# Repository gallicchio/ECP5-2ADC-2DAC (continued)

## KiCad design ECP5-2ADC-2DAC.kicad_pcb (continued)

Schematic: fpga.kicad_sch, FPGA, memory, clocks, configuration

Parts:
C5401, C5411, C5422, C5424, C5431, C5502, C5503, C5504, C5505, C5701, C5711: 100nF; C_0402_1005Metric; LCSC C1525
C5421: 10nF; C_0402_1005Metric; LCSC C15195
C5501, C5802, C5803, C5804, C5811, C5821, C5822, C5823, C5824, C5825, C5826, C5827: 10uF; C_0603_1608Metric; LCSC C96446
C5801: 22uF; C_0805_2012Metric; LCSC C45783
C5805, C5806, C5807, C5808, C5809, C5810, C5812, C5813, C5831, C5832, C5833, C5834, C5835, C5836, C5837, C5838, C5839, C5840, C5841, C5842, C5843: 100nF; C_0402_1005Metric_BGA; LCSC C1525
C5851, C5852, C5853, C5854, C5855, C5856, C5857: 22nF; C_0402_1005Metric_BGA; LCSC C1532
D301, D302, D303, D304, D305, D306, D307, D308: white; LED_0603_1608Metric; LCSC C2290
D309: XL-1615RGBC-RF; LED-ARRAY-SMD_4P-L1.6-W1.5-BR_XL-1615RGBC-RF; LCSC C965840
FB5811: 600R@100MHz; L_0603_1608Metric; LCSC C85833
J301, J302: SMA; SMA_BAT_Wireless_BWSMA-KWE-Z001; LCSC C496551
J303: PMOD A; PinSocket_2x06_P2.54mm_Horizontal; LCSC C22373932
J304: PMOD B; PinSocket_2x06_P2.54mm_Horizontal; LCSC C22373932
J305: JTAG; PinHeader_1x06_P2.54mm_Vertical; LCSC C2337
JP3001: TERM; PinHeader_1x02_P2.54mm_Vertical; LCSC C2337
R5401, R5411, R5412, R5413, R5423, R5601, R5602, R5603, R5604, R5605, R5606, R5607, R5608, R5611, R5612, R5613, R5614, R5615, R5616, R5617, R5618: 33R; R_0603_1608Metric; LCSC C23140
R5416, R5417, R5711, R5712, R5713, R5721, R5722, R5723, R5724: 4.7k; R_0603_1608Metric; LCSC C23162
R5421, R5431: 49.9R; R_0603_1608Metric; LCSC C23185
R5424, R5425, R5426, R5451, R5452, R5701, R5702, R5703: 10k; R_0603_1608Metric; LCSC C25804
R5427, R5441, R5442, R5443, R5444, R5445, R5446, R5447, R5448: 1k; R_0603_1608Metric; LCSC C21190
R5461, R5462, R5463: 330R; R_0603_1608Metric; LCSC C23138
SW301, SW302, SW303: SW_Push; SW-SMD_L3.9-W3.0-P4.45; LCSC C720477
U1: LFE5U-25F-6BG256C; BGA-256_14.0x14.0mm_Layout16x16_P0.8mm_Ball0.45mm_Pad0.32mm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; LCSC C1521614
U301: Si5351A-B-GTR; MSOP-10_3x3mm_P0.5mm; LCSC C504891
U302: TLV3501AIDBVR; SOT-23-6; LCSC C193413
U304: SN74LVC1G17DBVR; SOT-23-5; LCSC C7836
U305: W9825G6KH-6; TSOP-II-54_22.2x10.16mm_P0.8mm; LCSC C62246
U306: W25Q128JVSIQ; SOIC-8_5.3x5.3mm_P1.27mm; LCSC C97521
X301: FT5HNBPK25.0-T1; Oscillator_SMD_Fox_FT5H_5.0x3.2mm; LCSC C5742665
Y301: 25MHz; Crystal_SMD_3225-4Pin_3.2x2.5mm; LCSC C362338

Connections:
+1V1: C5801.1, C5802.1, C5803.1, C5804.1, C5805.1, C5806.1, C5807.1, C5808.1, C5809.1, C5810.1, U1.G6 (VCC), U1.G7 (VCC), U1.G9 (VCC), U1.L8 (VCC), U1.L9 (VCC), U1.L10 (VCC); also elsewhere on the board
+2V5: FB5811.1; also elsewhere on the board
+2V5_AUX: C5811.1, C5812.1, C5813.1, FB5811.2, U1.G11 (VCCAUX), U1.L7 (VCCAUX)
+3V3: C5401.1, C5411.1, C5431.1, C5501.1, C5502.1, C5503.1, C5504.1, C5505.1, C5701.1, C5821.1, C5822.1, C5823.1, C5824.1, C5825.1, C5826.1, C5827.1, C5831.1, C5832.1, C5833.1, C5834.1, C5835.1, C5836.1, C5837.1, C5838.1, C5839.1, C5840.1, C5841.1, C5842.1, C5843.1, C5851.1, C5852.1, C5853.1, C5854.1, C5855.1, C5856.1, C5857.1, D309.2 (A), J303.11, J303.12, J304.11, J304.12, J305.1, R5416.2, R5417.2, R5451.1, R5452.1, R5701.1, R5702.1, R5703.1, R5711.1, R5712.1, R5713.1, R5721.2, R5722.2, R5723.2, U1.F6 (VCCIO0), U1.F7 (VCCIO0), U1.F10 (VCCIO1), U1.F11 (VCCIO1), U1.H6 (VCCIO7), U1.H7 (VCCIO7), U1.H11 (VCCIO2), U1.J6 (VCCIO6), U1.J7 (VCCIO6), U1.J11 (VCCIO2), U1.K11 (VCCIO3), U1.L6 (VCCIO8), U1.L11 (VCCIO3), U1.P10 (P10_CFG1), U301.1 (VDD), U301.7 (VDDO), U304.5 (VCC), U305.1 (VDD), U305.3 (VDDQ), U305.9 (VDDQ), U305.14 (VDD), U305.27 (VDD), U305.43 (VDDQ), U305.49 (VDDQ), U306.8 (VCC), X301.4 (VCC); also elsewhere on the board
+3V3_ADC: C5422.1, R5424.1, U302.4 (V+); also elsewhere on the board
/ADC/ADC_A_CLK: U1.E4; also elsewhere on the board
/ADC/ADC_A_D0: U1.D1; also elsewhere on the board
/ADC/ADC_A_D1: U1.C1; also elsewhere on the board
/ADC/ADC_A_D2: U1.C2; also elsewhere on the board
/ADC/ADC_A_D3: U1.B1; also elsewhere on the board
/ADC/ADC_A_D4: U1.B2; also elsewhere on the board
/ADC/ADC_A_D5: U1.C3; also elsewhere on the board
/ADC/ADC_A_D6: U1.D3; also elsewhere on the board
/ADC/ADC_A_D7: U1.E3; also elsewhere on the board
/ADC/ADC_A_D8: U1.F3; also elsewhere on the board
/ADC/ADC_A_D9: U1.G3; also elsewhere on the board
/ADC/ADC_A_D10: U1.H3; also elsewhere on the board
/ADC/ADC_A_D11: U1.J5; also elsewhere on the board
/ADC/ADC_A_OTR: U1.J3 (J3_PCLK); also elsewhere on the board
/ADC/ADC_B_CLK: U1.R2; also elsewhere on the board
/ADC/ADC_B_D0: U1.G5; also elsewhere on the board
/ADC/ADC_B_D1: U1.F4; also elsewhere on the board
/ADC/ADC_B_D2: U1.G4; also elsewhere on the board
/ADC/ADC_B_D3: U1.H4; also elsewhere on the board
/ADC/ADC_B_D4: U1.J4; also elsewhere on the board
/ADC/ADC_B_D5: U1.K3; also elsewhere on the board
/ADC/ADC_B_D6: U1.H2; also elsewhere on the board
/ADC/ADC_B_D7: U1.G1 (G1_PCLK); also elsewhere on the board
/ADC/ADC_B_D8: U1.G2; also elsewhere on the board
/ADC/ADC_B_D9: U1.F1; also elsewhere on the board
/ADC/ADC_B_D10: U1.F2; also elsewhere on the board
/ADC/ADC_B_D11: U1.E1; also elsewhere on the board
/ADC/ADC_B_OTR: U1.E2; also elsewhere on the board
/ADC/ADC_DCS: U1.T6; also elsewhere on the board
/ADC/ADC_DFS: U1.R6; also elsewhere on the board
/ADC/ADC_PDWN_A: U1.R7; also elsewhere on the board
/ADC/ADC_PDWN_B: U1.T4; also elsewhere on the board
/DAC/DAC_CLK1: U1.N6; also elsewhere on the board
/DAC/DAC_CLK2: U1.M9; also elsewhere on the board
/DAC/DAC_MODE: U1.R8; also elsewhere on the board
/DAC/DAC_P1_D0: U1.L5; also elsewhere on the board
/DAC/DAC_P1_D1: U1.K5; also elsewhere on the board
/DAC/DAC_P1_D2: U1.N4; also elsewhere on the board
/DAC/DAC_P1_D3: U1.M4; also elsewhere on the board
/DAC/DAC_P1_D4: U1.L4 (L4_PCLK); also elsewhere on the board
/DAC/DAC_P1_D5: U1.K4 (K4_PCLK); also elsewhere on the board
/DAC/DAC_P1_D6: U1.P7; also elsewhere on the board
/DAC/DAC_P1_D7: U1.P6; also elsewhere on the board
/DAC/DAC_P1_D8: U1.P5; also elsewhere on the board
/DAC/DAC_P1_D9: U1.P4; also elsewhere on the board
/DAC/DAC_P1_D10: U1.P3; also elsewhere on the board
/DAC/DAC_P1_D11: U1.N3; also elsewhere on the board
/DAC/DAC_P1_D12: U1.M3; also elsewhere on the board
/DAC/DAC_P1_D13: U1.L3; also elsewhere on the board
/DAC/DAC_P2_D0: U1.L1 (L1_PCLK); also elsewhere on the board
/DAC/DAC_P2_D1: U1.L2 (L2_PCLK); also elsewhere on the board
/DAC/DAC_P2_D2: U1.M1 (M1_PCLK); also elsewhere on the board
/DAC/DAC_P2_D3: U1.M2 (M2_PCLK); also elsewhere on the board
/DAC/DAC_P2_D4: U1.N1; also elsewhere on the board
/DAC/DAC_P2_D5: U1.P1; also elsewhere on the board
/DAC/DAC_P2_D6: U1.P2; also elsewhere on the board
/DAC/DAC_P2_D7: U1.R1; also elsewhere on the board
/DAC/DAC_P2_D8: U1.T2; also elsewhere on the board
/DAC/DAC_P2_D9: U1.R3; also elsewhere on the board
/DAC/DAC_P2_D10: U1.T3; also elsewhere on the board
/DAC/DAC_P2_D11: U1.R4; also elsewhere on the board
/DAC/DAC_P2_D12: U1.M6; also elsewhere on the board
/DAC/DAC_P2_D13: U1.M5; also elsewhere on the board
/DAC/DAC_SLEEP: U1.R5; also elsewhere on the board
/DAC/DAC_WRT1: U1.N5; also elsewhere on the board
/DAC/DAC_WRT2: U1.P8; also elsewhere on the board
/FPGA, memory, clocks, configuration/CLK_EXT: R5423.2, U1.K2 (K2_PCLK)
/FPGA, memory, clocks, configuration/CLK_SI2: R5413.2, U1.K1 (K1_PCLK)
/FPGA, memory, clocks, configuration/ETH_INT_N: U1.F12; also elsewhere on the board
/FPGA, memory, clocks, configuration/ETH_MDC: U1.F15; also elsewhere on the board
/FPGA, memory, clocks, configuration/ETH_MDIO: U1.F16; also elsewhere on the board
/FPGA, memory, clocks, configuration/ETH_RST_N: U1.E16; also elsewhere on the board
/FPGA, memory, clocks, configuration/ETH_RXC: U1.E8 (E8_PCLK); also elsewhere on the board
/FPGA, memory, clocks, configuration/ETH_RXD0: U1.F14; also elsewhere on the board
/FPGA, memory, clocks, configuration/ETH_RXD1: U1.E14; also elsewhere on the board
/FPGA, memory, clocks, configuration/ETH_RXD2: U1.D14; also elsewhere on the board
/FPGA, memory, clocks, configuration/ETH_RXD3: U1.C14; also elsewhere on the board
/FPGA, memory, clocks, configuration/ETH_RX_CTL: U1.F13; also elsewhere on the board
/FPGA, memory, clocks, configuration/ETH_TXC: U1.E15; also elsewhere on the board
/FPGA, memory, clocks, configuration/ETH_TXD0: U1.C16; also elsewhere on the board
/FPGA, memory, clocks, configuration/ETH_TXD1: U1.C15; also elsewhere on the board
/FPGA, memory, clocks, configuration/ETH_TXD2: U1.B16; also elsewhere on the board
/FPGA, memory, clocks, configuration/ETH_TXD3: U1.B15; also elsewhere on the board
/FPGA, memory, clocks, configuration/ETH_TX_CTL: U1.D16; also elsewhere on the board
/FPGA, memory, clocks, configuration/FTDI_DTR: U1.G15; also elsewhere on the board
/FPGA, memory, clocks, configuration/FTDI_RTS: U1.G16 (G16_PCLK); also elsewhere on the board
/FPGA, memory, clocks, configuration/GPDI_CEC: U1.K12; also elsewhere on the board
/FPGA, memory, clocks, configuration/GPDI_CK_N: U1.K15 (K15_PCLK); also elsewhere on the board
/FPGA, memory, clocks, configuration/GPDI_CK_P: U1.K16 (K16_PCLK); also elsewhere on the board
/FPGA, memory, clocks, configuration/GPDI_D0_N: U1.J15 (J15_PCLK); also elsewhere on the board
/FPGA, memory, clocks, configuration/GPDI_D0_P: U1.J16 (J16_PCLK); also elsewhere on the board
/FPGA, memory, clocks, configuration/GPDI_D1_N: U1.K14; also elsewhere on the board
/FPGA, memory, clocks, configuration/GPDI_D1_P: U1.J14 (J14_PCLK); also elsewhere on the board
/FPGA, memory, clocks, configuration/GPDI_D2_N: U1.J12; also elsewhere on the board
/FPGA, memory, clocks, configuration/GPDI_D2_P: U1.J13; also elsewhere on the board
/FPGA, memory, clocks, configuration/GPDI_HPD: U1.K13 (K13_PCLK); also elsewhere on the board
/FPGA, memory, clocks, configuration/GPDI_SCL: U1.M12; also elsewhere on the board
/FPGA, memory, clocks, configuration/GPDI_SDA: U1.N13; also elsewhere on the board
/FPGA, memory, clocks, configuration/I2C_SCL: R5417.1, U1.A15, U301.4 (SCL)
/FPGA, memory, clocks, configuration/I2C_SDA: R5416.1, U1.E13, U301.5 (SDA)
/FPGA, memory, clocks, configuration/JTAG_TCK: J305.2, R5724.1, U1.T10 (T10_TCK); also elsewhere on the board
/FPGA, memory, clocks, configuration/JTAG_TDI: J305.4, R5722.1, U1.R11 (R11_TDI); also elsewhere on the board
/FPGA, memory, clocks, configuration/JTAG_TDO: J305.5, R5723.1, U1.M10 (M10_TDO); also elsewhere on the board
/FPGA, memory, clocks, configuration/JTAG_TMS: J305.3, R5721.1, U1.T11 (T11_TMS); also elsewhere on the board
/FPGA, memory, clocks, configuration/LED2: R5443.1, U1.E10
/FPGA, memory, clocks, configuration/LED3: R5444.1, U1.E11
/FPGA, memory, clocks, configuration/LED4: R5445.1, U1.G12
/FPGA, memory, clocks, configuration/LED5: R5446.1, U1.E12
/FPGA, memory, clocks, configuration/LED6: R5447.1, U1.A14
/FPGA, memory, clocks, configuration/LED7: R5448.1, U1.B14
/FPGA, memory, clocks, configuration/LED_B: R5463.1, U1.R12
/FPGA, memory, clocks, configuration/LED_G: R5462.1, U1.R13
/FPGA, memory, clocks, configuration/LED_R: R5461.1, U1.R14
/FPGA, memory, clocks, configuration/PMODA_0: R5601.1, U1.R15
/FPGA, memory, clocks, configuration/PMODA_1: R5602.1, U1.P15
/FPGA, memory, clocks, configuration/PMODA_2: R5603.1, U1.N16
/FPGA, memory, clocks, configuration/PMODA_3: R5604.1, U1.M16 (M16_PCLK)
/FPGA, memory, clocks, configuration/PMODA_4: R5605.2, U1.R16
/FPGA, memory, clocks, configuration/PMODA_5: R5606.2, U1.P16
/FPGA, memory, clocks, configuration/PMODA_6: R5607.2, U1.M15 (M15_PCLK)
/FPGA, memory, clocks, configuration/PMODA_7: R5608.2, U1.L15 (L15_PCLK)
/FPGA, memory, clocks, configuration/PMODB_0: R5611.1, U1.L16 (L16_PCLK)
/FPGA, memory, clocks, configuration/PMODB_1: R5612.1, U1.N14
/FPGA, memory, clocks, configuration/PMODB_2: R5613.1, U1.M14
/FPGA, memory, clocks, configuration/PMODB_3: R5614.1, U1.L14
/FPGA, memory, clocks, configuration/PMODB_4: R5615.2, U1.P14
/FPGA, memory, clocks, configuration/PMODB_5: R5616.2, U1.M13
/FPGA, memory, clocks, configuration/PMODB_6: R5617.2, U1.L13 (L13_PCLK)
/FPGA, memory, clocks, configuration/PMODB_7: R5618.2, U1.L12
/FPGA, memory, clocks, configuration/SDRAM_A0: U1.A5, U305.23 (A0)
/FPGA, memory, clocks, configuration/SDRAM_A1: U1.B5, U305.24 (A1)
/FPGA, memory, clocks, configuration/SDRAM_A2: U1.A4, U305.25 (A2)
/FPGA, memory, clocks, configuration/SDRAM_A3: U1.B4, U305.26 (A3)
/FPGA, memory, clocks, configuration/SDRAM_A4: U1.B13, U305.29 (A4)
/FPGA, memory, clocks, configuration/SDRAM_A5: U1.A13, U305.30 (A5)
/FPGA, memory, clocks, configuration/SDRAM_A6: U1.B12, U305.31 (A6)
/FPGA, memory, clocks, configuration/SDRAM_A7: U1.A12, U305.32 (A7)
/FPGA, memory, clocks, configuration/SDRAM_A8: U1.B11, U305.33 (A8)
/FPGA, memory, clocks, configuration/SDRAM_A9: U1.A11, U305.34 (A9)
/FPGA, memory, clocks, configuration/SDRAM_A10: U1.B6, U305.22 (A10)
/FPGA, memory, clocks, configuration/SDRAM_A11: U1.B10, U305.35 (A11)
/FPGA, memory, clocks, configuration/SDRAM_A12: U1.C13, U305.36 (A12)
/FPGA, memory, clocks, configuration/SDRAM_BA0: U1.B7 (B7_PCLK), U305.20 (BA0)
/FPGA, memory, clocks, configuration/SDRAM_BA1: U1.A6, U305.21 (BA1)
/FPGA, memory, clocks, configuration/SDRAM_CAS_N: U1.A8 (A8_PCLK), U305.17 (~CAS)
/FPGA, memory, clocks, configuration/SDRAM_CKE: U1.C12, U305.37 (CKE)
/FPGA, memory, clocks, configuration/SDRAM_CLK: U1.C11, U305.38 (CLK)
/FPGA, memory, clocks, configuration/SDRAM_CS_N: U1.A7 (A7_PCLK), U305.19 (~CS)
/FPGA, memory, clocks, configuration/SDRAM_DQ0: U1.D6, U305.2 (DQ0)
/FPGA, memory, clocks, configuration/SDRAM_DQ1: U1.D5, U305.4 (DQ1)
/FPGA, memory, clocks, configuration/SDRAM_DQ2: U1.D4, U305.5 (DQ2)
/FPGA, memory, clocks, configuration/SDRAM_DQ3: U1.C6, U305.7 (DQ3)
/FPGA, memory, clocks, configuration/SDRAM_DQ4: U1.C5, U305.8 (DQ4)
/FPGA, memory, clocks, configuration/SDRAM_DQ5: U1.C4, U305.10 (DQ5)
/FPGA, memory, clocks, configuration/SDRAM_DQ6: U1.A10, U305.11 (DQ6)
/FPGA, memory, clocks, configuration/SDRAM_DQ7: U1.B9 (B9_PCLK), U305.13 (DQ7)
/FPGA, memory, clocks, configuration/SDRAM_DQ8: U1.C9 (C9_PCLK), U305.42 (DQ8)
/FPGA, memory, clocks, configuration/SDRAM_DQ9: U1.C8 (C8_PCLK), U305.44 (DQ9)
/FPGA, memory, clocks, configuration/SDRAM_DQ10: U1.D13, U305.45 (DQ10)
/FPGA, memory, clocks, configuration/SDRAM_DQ11: U1.D12, U305.47 (DQ11)
/FPGA, memory, clocks, configuration/SDRAM_DQ12: U1.D11, U305.48 (DQ12)
/FPGA, memory, clocks, configuration/SDRAM_DQ13: U1.D10, U305.50 (DQ13)
/FPGA, memory, clocks, configuration/SDRAM_DQ14: U1.D9, U305.51 (DQ14)
/FPGA, memory, clocks, configuration/SDRAM_DQ15: U1.D8 (D8_PCLK), U305.53 (DQ15)
/FPGA, memory, clocks, configuration/SDRAM_DQMH: U1.C10, U305.39 (DQMH)
/FPGA, memory, clocks, configuration/SDRAM_DQML: U1.A9, U305.15 (DQML)
/FPGA, memory, clocks, configuration/SDRAM_RAS_N: U1.B8 (B8_PCLK), U305.18 (~RAS)
/FPGA, memory, clocks, configuration/SDRAM_WE_N: U1.E9, U305.16 (~WE)
/FPGA, memory, clocks, configuration/SD_CLK: U1.T15; also elsewhere on the board
/FPGA, memory, clocks, configuration/SD_CMD: U1.P12; also elsewhere on the board
/FPGA, memory, clocks, configuration/SD_D0: U1.T14; also elsewhere on the board
/FPGA, memory, clocks, configuration/SD_D1: U1.T13; also elsewhere on the board
/FPGA, memory, clocks, configuration/SD_D2: U1.P13; also elsewhere on the board
/FPGA, memory, clocks, configuration/SD_D3: U1.N12; also elsewhere on the board
/FPGA, memory, clocks, configuration/UART_RX: U1.H15; also elsewhere on the board
/FPGA, memory, clocks, configuration/UART_TX: U1.H14; also elsewhere on the board
/FPGA, memory, clocks, configuration/USB_DN: U1.G13; also elsewhere on the board
/FPGA, memory, clocks, configuration/USB_DP: U1.G14; also elsewhere on the board
/FPGA, memory, clocks, configuration/USB_PULLUP: U1.H13; also elsewhere on the board
GND: C5401.2, C5411.2, C5422.2, C5424.2, C5431.2, C5501.2, C5502.2, C5503.2, C5504.2, C5505.2, C5701.2, C5711.2, C5801.2, C5802.2, C5803.2, C5804.2, C5805.2, C5806.2, C5807.2, C5808.2, C5809.2, C5810.2, C5811.2, C5812.2, C5813.2, C5821.2, C5822.2, C5823.2, C5824.2, C5825.2, C5826.2, C5827.2, C5831.2, C5832.2, C5833.2, C5834.2, C5835.2, C5836.2, C5837.2, C5838.2, C5839.2, C5840.2, C5841.2, C5842.2, C5843.2, C5851.2, C5852.2, C5853.2, C5854.2, C5855.2, C5856.2, C5857.2, D301.1 (K), D302.1 (K), D303.1 (K), D304.1 (K), D305.1 (K), D306.1 (K), D307.1 (K), D308.1 (K), J301.2, J302.2, J303.9, J303.10, J304.9, J304.10, J305.6, JP3001.1 (A), R5425.2, R5724.2, SW301.1, SW302.1, SW303.2, U1.A1 (GND), U1.A16 (GND), U1.D2 (GND), U1.D15 (GND), U1.F8 (GND), U1.F9 (GND), U1.G8 (GND), U1.G10 (GND), U1.H1 (GND), U1.H8 (GND), U1.H9 (GND), U1.H10 (GND), U1.H16 (GND), U1.J8 (GND), U1.J9 (GND), U1.J10 (GND), U1.K6 (GND), U1.K7 (GND), U1.K8 (GND), U1.K9 (GND), U1.K10 (GND), U1.N2 (GND), U1.N10 (N10_CFG0), U1.N15 (GND), U1.R10 (R10_CFG2), U1.T1 (GND), U1.T5 (GND), U1.T12 (GND), U1.T16 (GND), U301.8 (GND), U302.2 (V-), U302.6 (SHDN), U304.3 (GND), U305.6 (VSSQ), U305.12 (VSSQ), U305.28 (VSS), U305.41 (VSS), U305.46 (VSSQ), U305.52 (VSSQ), U305.54 (VSS), U306.4 (GND), X301.1 (GND), X301.2 (GND), Y301.2 (G), Y301.4 (G); also elsewhere on the board
unnamed: C5421.1, J301.1, R5421.1
unnamed: C5421.2, R5427.1
unnamed: D301.2 (A), R5441.2
unnamed: D302.2 (A), R5442.2
unnamed: D303.2 (A), R5443.2
unnamed: D304.2 (A), R5444.2
unnamed: D305.2 (A), R5445.2
unnamed: D306.2 (A), R5446.2
unnamed: D307.2 (A), R5447.2
unnamed: D308.2 (A), R5448.2
unnamed: D309.3 (B), R5463.2
unnamed: D309.4 (G), R5462.2
unnamed: D309.1 (R), R5461.2
unnamed: J302.1, R5431.2
unnamed: J303.1, R5601.2
unnamed: J303.2, R5605.1
unnamed: J303.3, R5602.2
unnamed: J303.4, R5606.1
unnamed: J303.5, R5603.2
unnamed: J303.6, R5607.1
unnamed: J303.7, R5604.2
unnamed: J303.8, R5608.1
unnamed: J304.1, R5611.2
unnamed: J304.2, R5615.1
unnamed: J304.3, R5612.2
unnamed: J304.4, R5616.1
unnamed: J304.5, R5613.2
unnamed: J304.6, R5617.1
unnamed: J304.7, R5614.2
unnamed: J304.8, R5618.1
unnamed: JP3001.2 (B), R5421.2
unnamed: R5423.1, U302.5
unnamed: R5431.1, U304.4
unnamed: R5441.1, U1.E6
unnamed: R5442.1, U1.E5
unnamed: R5451.2, SW301.2, U1.A3
unnamed: R5452.2, SW302.2, U1.B3
unnamed: U1.A2, U304.2
unnamed: R5401.2, U1.C7 (C7_PCLK)
unnamed: R5411.2, U1.D7 (D7_PCLK)
unnamed: R5412.2, U1.E7 (E7_PCLK)
unnamed: U1.N9 (N9_CCLK/MCLK), U306.6 (CLK)
unnamed: R5713.2, U1.P9 (P9_DONE)
unnamed: C5711.1, R5711.2, SW303.1, U1.R9 (R9_PROGRAMN)
unnamed: R5712.2, U1.T9 (T9_INITN)
unnamed: R5411.1, U301.10 (CLK0)
unnamed: R5412.1, U301.9 (CLK1)
unnamed: R5413.1, U301.6 (CLK2)
unnamed: U301.2 (XA), Y301.1
unnamed: U301.3 (XB), Y301.3
unnamed: R5426.1, R5427.2, U302.3 (+)
unnamed: C5424.1, R5424.2, R5425.1, R5426.2, U302.1 (-)
unnamed: U1.T8, U306.5 (DI/IO0)
unnamed: U1.T7, U306.2 (DO/IO1)
unnamed: R5703.2, U1.N8, U306.1 (~CS)
unnamed: R5702.2, U1.N7, U306.7 (~HOLD/IO3)
unnamed: R5701.2, U1.M7, U306.3 (~WP/IO2)
unnamed: R5401.1, X301.3 (OUT)

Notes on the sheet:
PROGRAMN, INITN, DONE: 4.7 k to VCCIO8
press: reload from the flash
VCCIO: 100 nF per pin
Si5351A: three programmable clocks, 2.5 kHz to 200 MHz
FPGA: Lattice ECP5 LFE5U-25F-6BG256C, 32 MB SDRAM, 16 MB flash, clocks, configuration
10 pF crystal, load capacitors inside; this I2C bus is the Si5351's alone (the HDMI DDC is a second bus)
bank 3: SD card, USB, serial, Pmods
CLK IN: an external reference or sample clock
quad SPI flash on the sysCONFIG pins: boots the FPGA and holds the bitstream
100 nF: configuration starts 0.5 ms after VCCIO8
I2C pull-ups
bank 8: sysCONFIG, flash, JTAG, slow controls
4.7 k: TMS, TDI, TDO up; TCK down
VCCIO: 10 µF per bank
bank 7: ADC
15 of the 39 SDRAM lines live on bank 0
shunt in = 50 Ω
VCCAUX: ferrite + 10 µF + 100 nF per pin
user LEDs 0-7, white, active high, ~1 mA
RGB LED (common anode): drive a cathode low to light it, ~2 mA
SDRAM: 100 nF per VDD/VDDQ pair
FPGA power: 6 x VCC (1.1 V core), 2 x VCCAUX (2.5 V through a ferrite), 13 x VCCIO (3.3 V, all banks), 27 x GND
VCCIO: 22 nF per bank (as the Icepi Zero)
CFG[2:0] = 010: master SPI boot from the flash (as the Icepi Zero)
mid-rail 1.65 V: -IN directly, +IN through 10 k
CLK OUT: sync a second board
WP, HOLD, CS: 10 k up
bank 2: Ethernet, HDMI
bank 6: DAC
bank 1: SDRAM
BTN0 = reset, BTN1 = user; active low
VCC: 3 x 10 µF + 100 nF per pin (Lattice checklist)
25 MHz TCXO ±2.5 ppm: the system clock
bank 0
10 MHz sine from a GPSDO (0.3 V peak or more), or any 0.5 to 3.3 V square wave to 80 MHz. 50 Ω if the shunt is in. AC coupled into a TLV3501 comparator on the ADC's low-noise 3.3 V through 1 kΩ, which holds its input clamps under 10 mA for a ±10 V generator: +IN biased to mid-rail through 10 kΩ, -I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
Any address or data bit can be swapped for routing: the SDRAM controller does not care which ball is A5. Clocked by an FPGA ODDR at up to 100 MHz, no termination, 3.3 V LVCMOS.
Pmod sockets, 0.9 inch apart on the board edge so a double-width module spans both. 33 Ω series; Pmod pins 1-4 = IO0-3, 7-10 = IO4-7, 5/11 ground, 6/12 3.3 V (pads 1,3,5,7 / 2,4,6,8 / 9,10 / 11,12 in KiCad's odd/even numbering). Both buses are drawn; the labels on the socket end are the same bus me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
JTAG header: the same four signals the FT2232H drives (USB sheet). TCK pulled down, TMS/TDI/TDO pulled up (Lattice checklist). To use an external programmer here, fit JP501 FTDI OFF (USB sheet) first: it holds the FT2232H in reset, so its TXD / TCK output cannot fight. These four local labels and t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
Any FPGA clock, 50 Ω source terminated: 3.3 V open circuit, 1.65 V into 50 Ω; the other board's CLK IN squares it up.
One box per I/O bank, in the position the bank has on the package: 7 and 6 on the west (ADC above, DAC below); 0 and 1 on the north (clocks, I2C, LEDs, buttons; the SDRAM); 2 and 3 on the east (Ethernet and HDMI; SD card, USB, serial, Pmods); 8 on the south (sysCONFIG: SPI flash, JTAG, slow control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

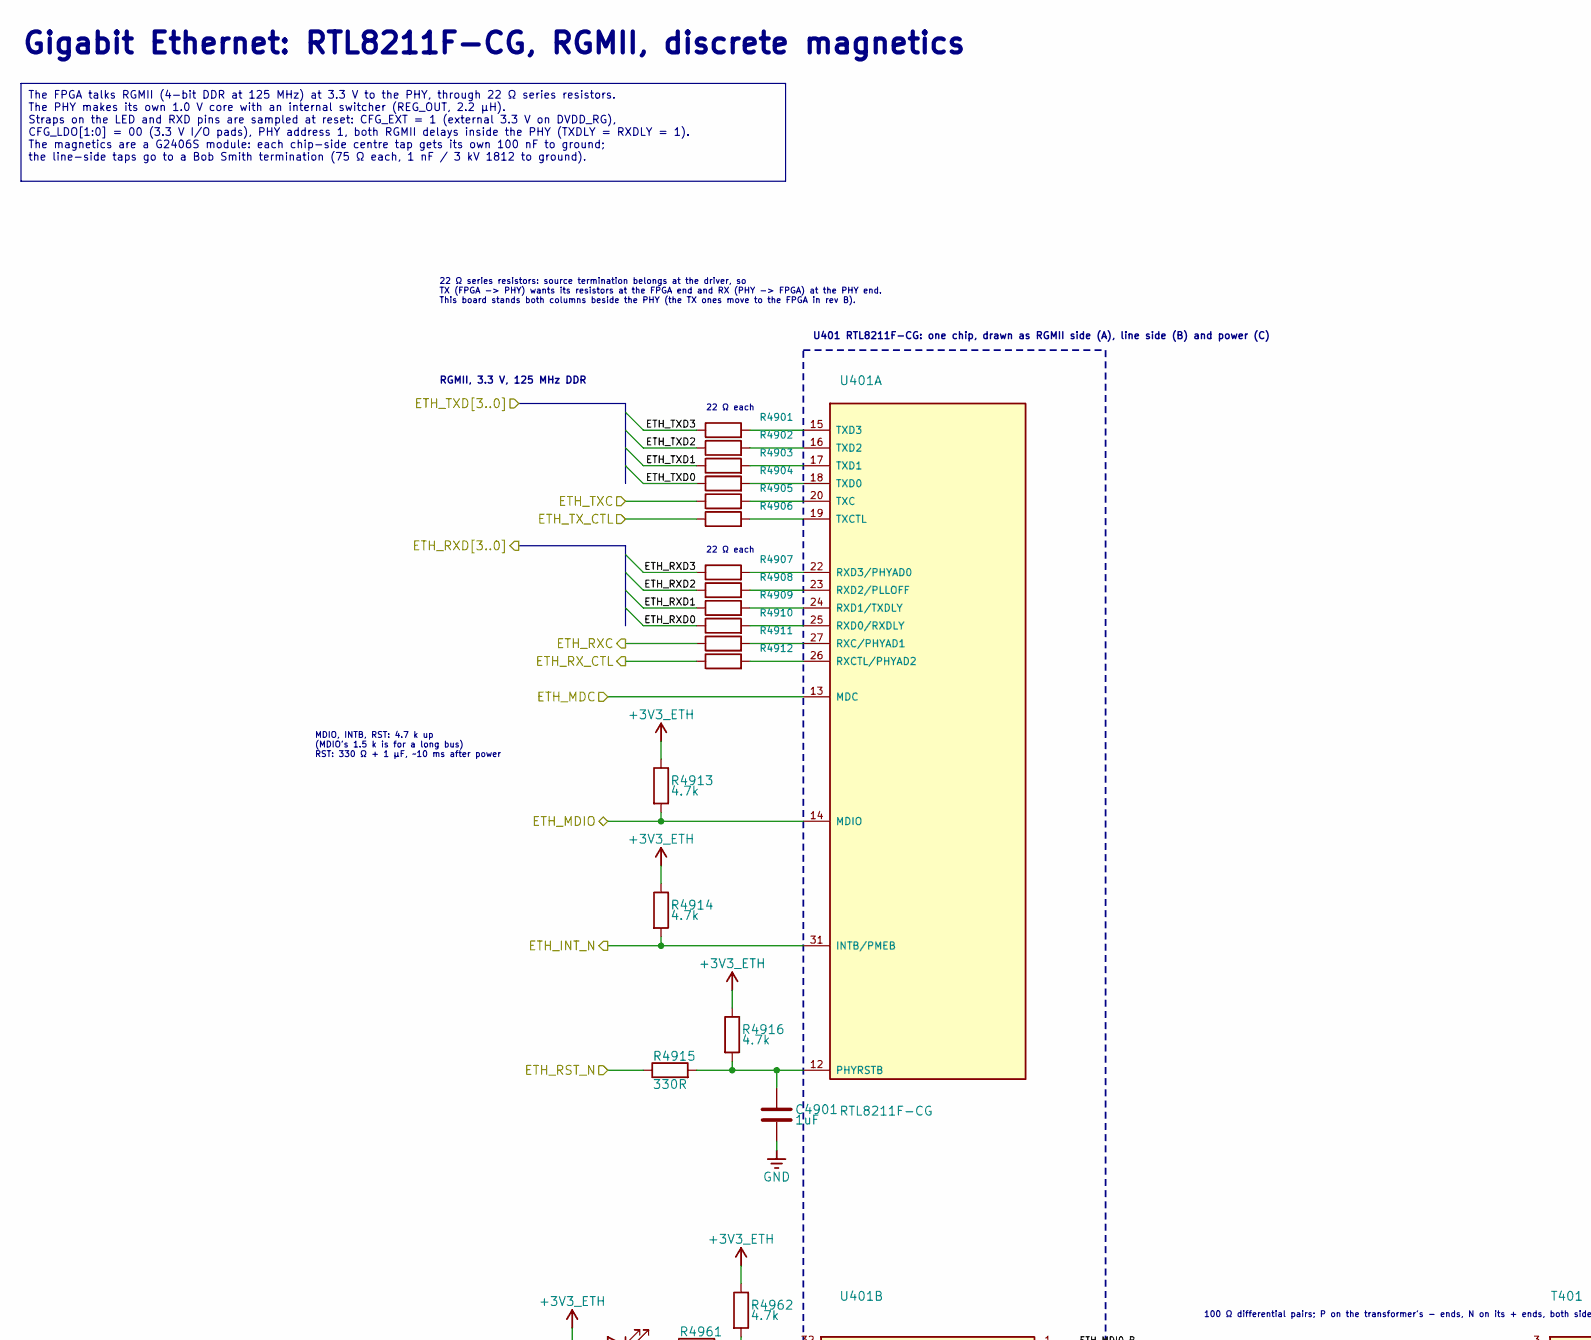
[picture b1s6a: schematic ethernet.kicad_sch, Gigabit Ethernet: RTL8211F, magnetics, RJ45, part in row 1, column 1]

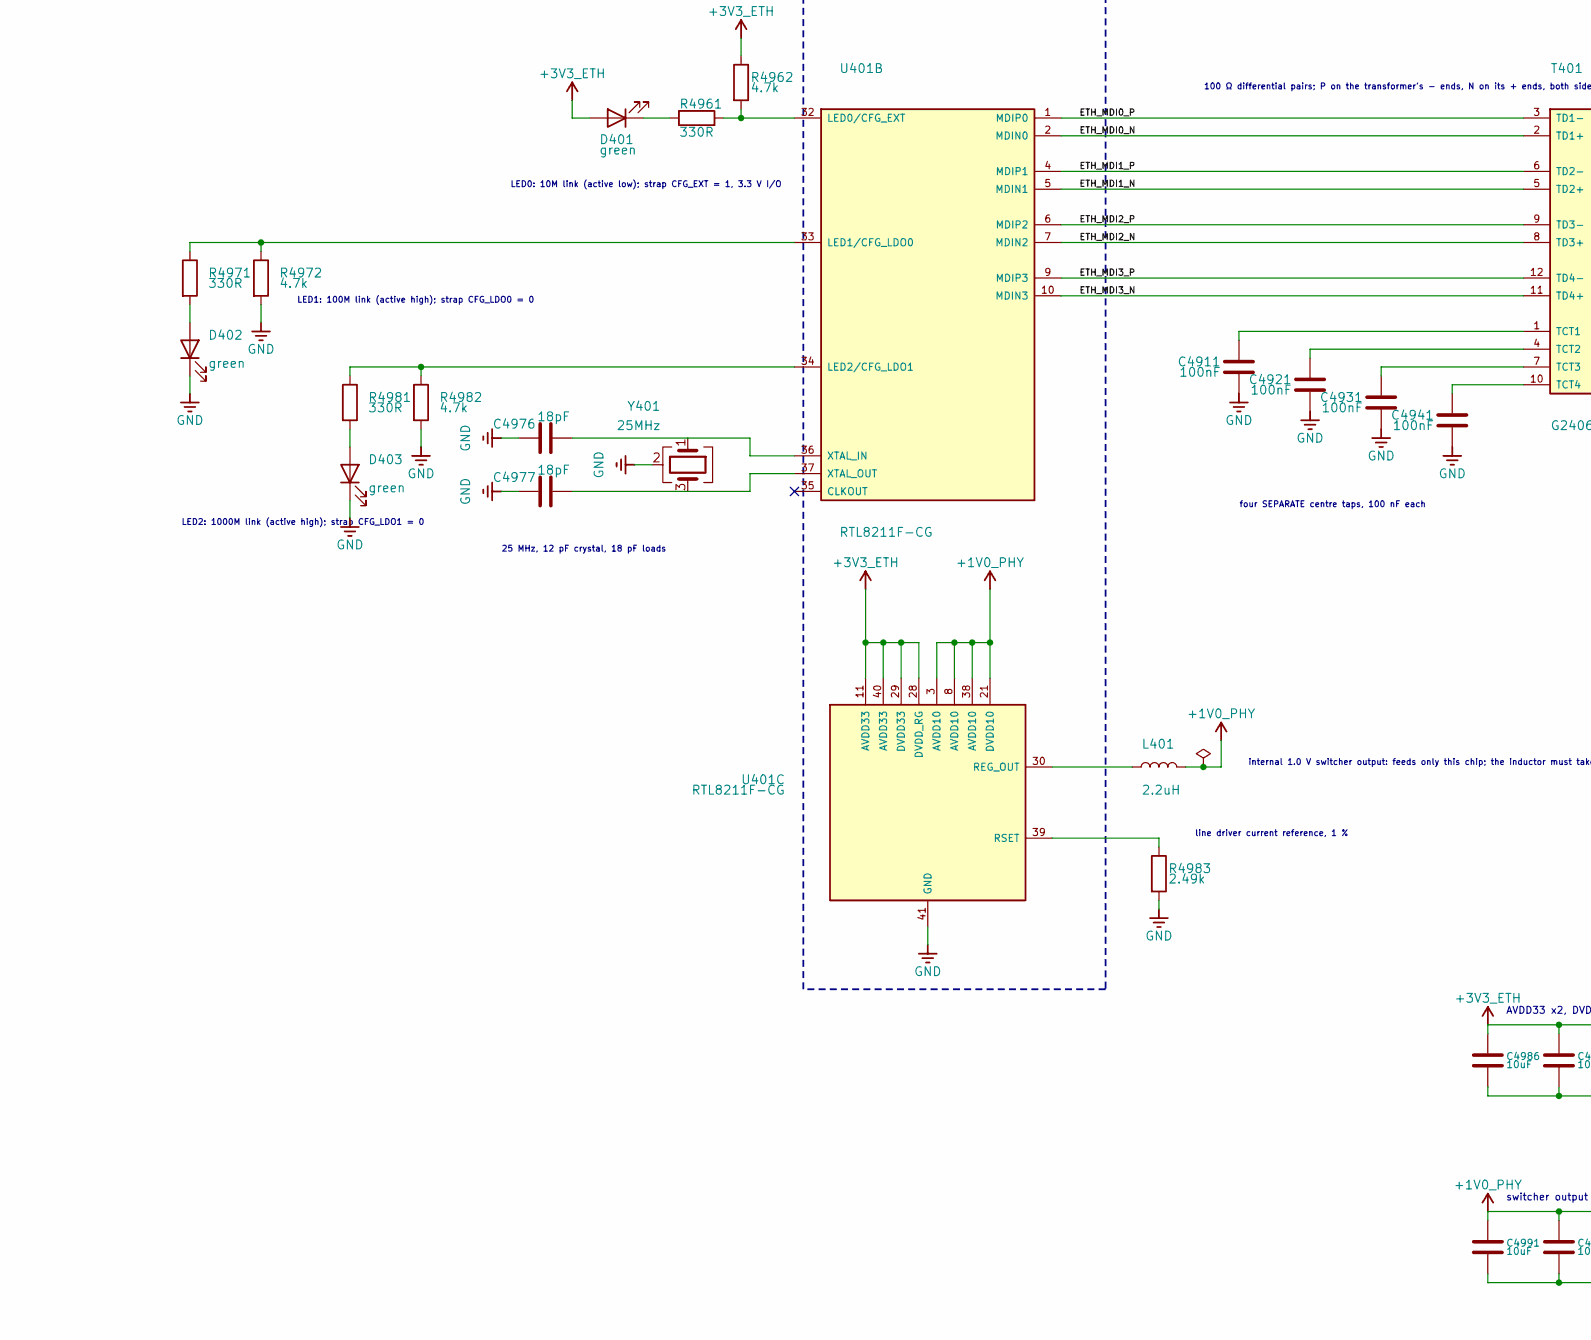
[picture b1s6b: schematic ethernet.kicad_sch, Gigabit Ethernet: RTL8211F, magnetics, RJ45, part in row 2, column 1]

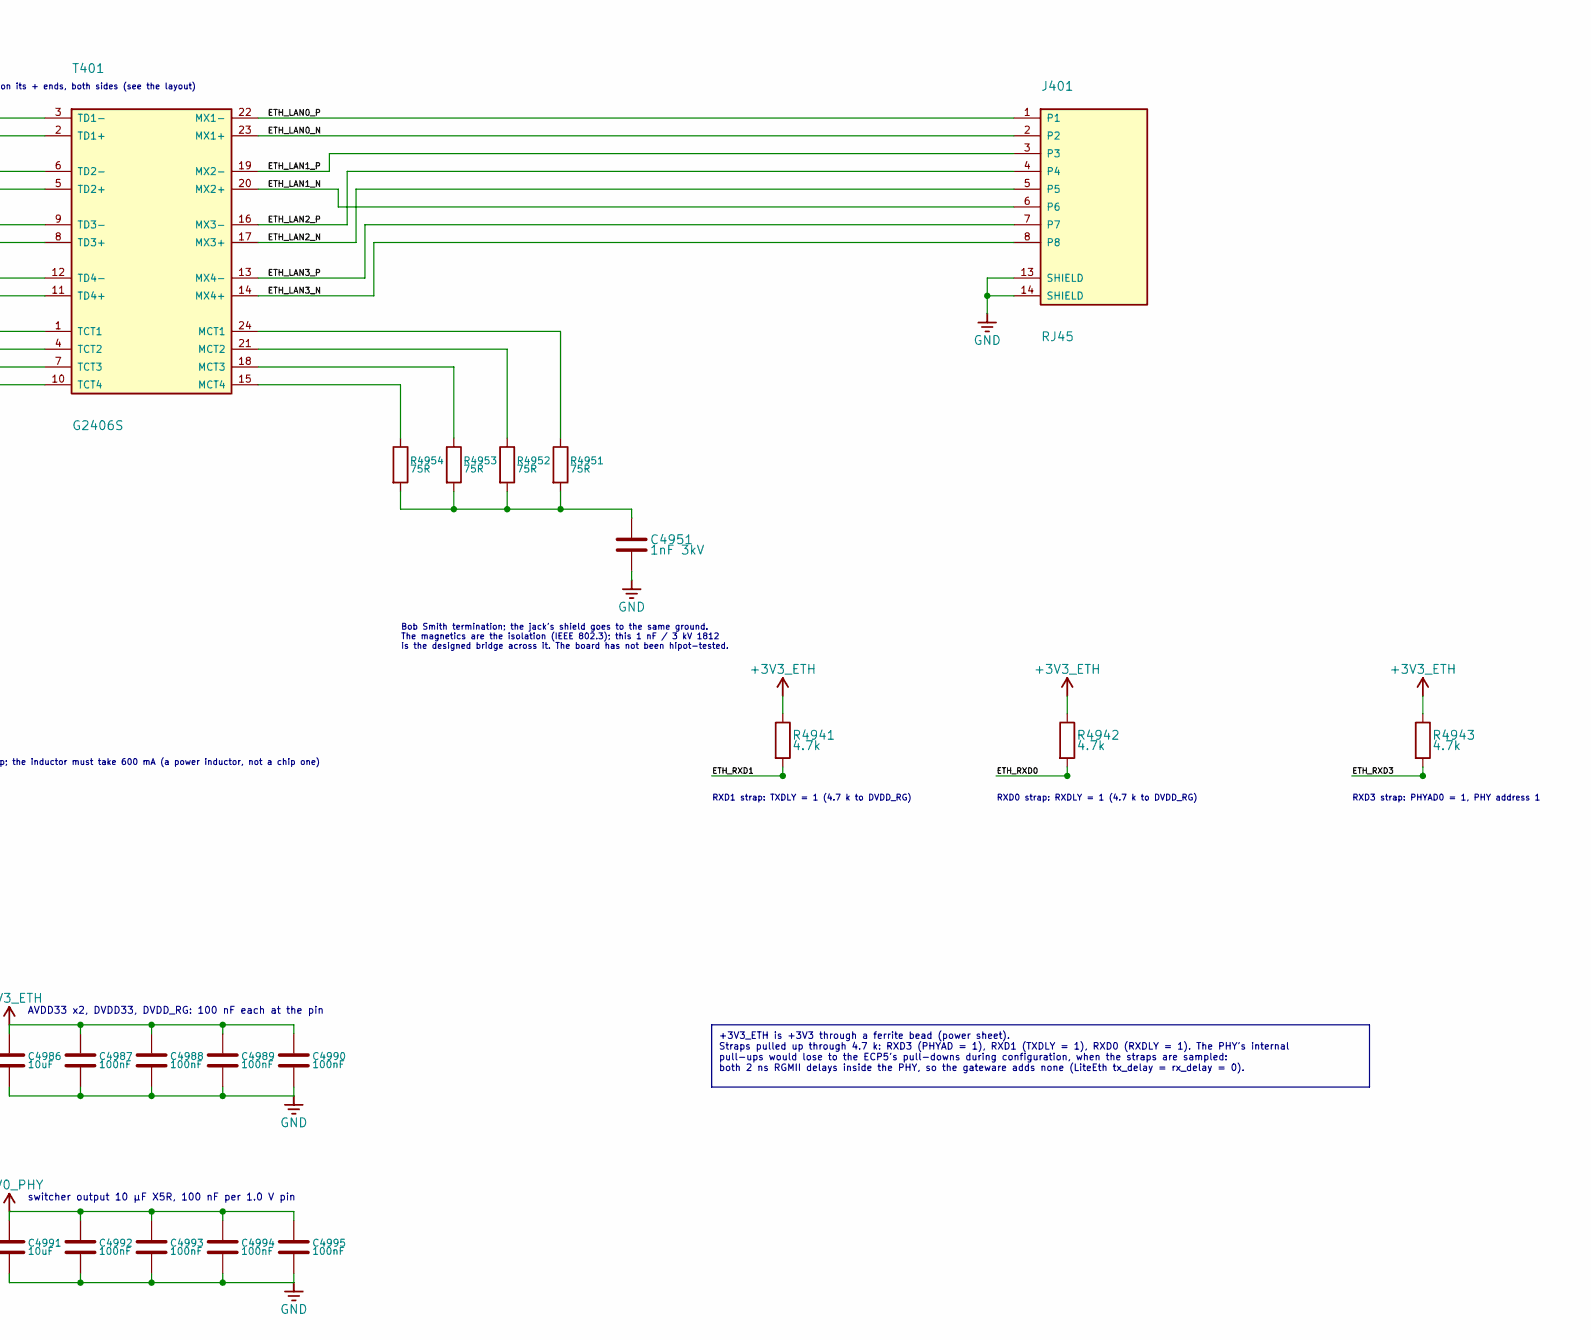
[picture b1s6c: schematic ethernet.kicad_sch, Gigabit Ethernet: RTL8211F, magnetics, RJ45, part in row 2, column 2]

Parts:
C4901: 1uF; C_0402_1005Metric; LCSC C52923
C4911, C4921, C4931, C4941, C4987, C4988, C4989, C4990, C4992, C4993, C4994, C4995: 100nF; C_0402_1005Metric; LCSC C1525
C4951: 1nF 3kV; C_1812_4532Metric; LCSC C692296
C4976, C4977: 18pF; C_0402_1005Metric; LCSC C1549
C4986, C4991: 10uF; C_0603_1608Metric; LCSC C96446
D401, D402, D403: green; LED_0603_1608Metric; LCSC C12624
J401: RJ45; RJ45-TH_R-RJ45R08P-C000; LCSC C386757
L401: 2.2uH; IND-SMD_L4.0-W4.0; LCSC C279948
R4901, R4902, R4903, R4904, R4905, R4906, R4907, R4908, R4909, R4910, R4911, R4912: 22R; R_0603_1608Metric; LCSC C23345
R4913, R4914, R4916, R4941, R4942, R4943, R4962, R4972, R4982: 4.7k; R_0603_1608Metric; LCSC C23162
R4915, R4961, R4971, R4981: 330R; R_0603_1608Metric; LCSC C23138
R4951, R4952, R4953, R4954: 75R; R_0603_1608Metric; LCSC C4275
R4983: 2.49k; R_0603_1608Metric; LCSC C22908
T401: G2406S; SMD-24_L15.1-W7.1-P1.00-LS10.0-BL; LCSC C507595
U401: RTL8211F-CG; QFN-40-1EP_5x5mm_P0.4mm_EP3.6x3.6mm; LCSC C187932
Y401: 25MHz; Crystal_SMD_3225-4Pin_3.2x2.5mm; LCSC C9006

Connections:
+1V0_PHY: C4991.1, C4992.1, C4993.1, C4994.1, C4995.1, L401.2, U401.3 (AVDD10), U401.8 (AVDD10), U401.21 (DVDD10), U401.38 (AVDD10); also elsewhere on the board
+3V3_ETH: C4986.1, C4987.1, C4988.1, C4989.1, C4990.1, D401.2 (A), R4913.1, R4914.1, R4916.1, R4941.1, R4942.1, R4943.1, R4962.1, U401.11 (AVDD33), U401.28 (DVDD_RG), U401.29 (DVDD33), U401.40 (AVDD33); also elsewhere on the board
/FPGA, memory, clocks, configuration/ETH_INT_N: R4914.2, U401.31 (INTB/PMEB); also elsewhere on the board
/FPGA, memory, clocks, configuration/ETH_MDC: U401.13 (MDC); also elsewhere on the board
/FPGA, memory, clocks, configuration/ETH_MDIO: R4913.2, U401.14 (MDIO); also elsewhere on the board
/FPGA, memory, clocks, configuration/ETH_RST_N: R4915.1; also elsewhere on the board
/FPGA, memory, clocks, configuration/ETH_RXC: R4911.1; also elsewhere on the board
/FPGA, memory, clocks, configuration/ETH_RXD0: R4910.1, R4942.2; also elsewhere on the board
/FPGA, memory, clocks, configuration/ETH_RXD1: R4909.1, R4941.2; also elsewhere on the board
/FPGA, memory, clocks, configuration/ETH_RXD2: R4908.1; also elsewhere on the board
/FPGA, memory, clocks, configuration/ETH_RXD3: R4907.1, R4943.2; also elsewhere on the board
/FPGA, memory, clocks, configuration/ETH_RX_CTL: R4912.1; also elsewhere on the board
/FPGA, memory, clocks, configuration/ETH_TXC: R4905.1; also elsewhere on the board
/FPGA, memory, clocks, configuration/ETH_TXD0: R4904.1; also elsewhere on the board
/FPGA, memory, clocks, configuration/ETH_TXD1: R4903.1; also elsewhere on the board
/FPGA, memory, clocks, configuration/ETH_TXD2: R4902.1; also elsewhere on the board
/FPGA, memory, clocks, configuration/ETH_TXD3: R4901.1; also elsewhere on the board
/FPGA, memory, clocks, configuration/ETH_TX_CTL: R4906.1; also elsewhere on the board
/Gigabit Ethernet/ETH_LAN0_N: J401.2, T401.23 (MX1+)
/Gigabit Ethernet/ETH_LAN0_P: J401.1, T401.22 (MX1-)
/Gigabit Ethernet/ETH_LAN1_N: J401.6, T401.20 (MX2+)
/Gigabit Ethernet/ETH_LAN1_P: J401.3, T401.19 (MX2-)
/Gigabit Ethernet/ETH_LAN2_N: J401.5, T401.17 (MX3+)
/Gigabit Ethernet/ETH_LAN2_P: J401.4, T401.16 (MX3-)
/Gigabit Ethernet/ETH_LAN3_N: J401.8, T401.14 (MX4+)
/Gigabit Ethernet/ETH_LAN3_P: J401.7, T401.13 (MX4-)
/Gigabit Ethernet/ETH_MDI0_N: T401.2 (TD1+), U401.2 (MDIN0)
/Gigabit Ethernet/ETH_MDI0_P: T401.3 (TD1-), U401.1 (MDIP0)
/Gigabit Ethernet/ETH_MDI1_N: T401.5 (TD2+), U401.5 (MDIN1)
/Gigabit Ethernet/ETH_MDI1_P: T401.6 (TD2-), U401.4 (MDIP1)
/Gigabit Ethernet/ETH_MDI2_N: T401.8 (TD3+), U401.7 (MDIN2)
/Gigabit Ethernet/ETH_MDI2_P: T401.9 (TD3-), U401.6 (MDIP2)
/Gigabit Ethernet/ETH_MDI3_N: T401.11 (TD4+), U401.10 (MDIN3)
/Gigabit Ethernet/ETH_MDI3_P: T401.12 (TD4-), U401.9 (MDIP3)
GND: C4901.2, C4911.2, C4921.2, C4931.2, C4941.2, C4951.2, C4976.1, C4977.1, C4986.2, C4987.2, C4988.2, C4989.2, C4990.2, C4991.2, C4992.2, C4993.2, C4994.2, C4995.2, D402.1 (K), D403.1 (K), J401.13 (SHIELD), J401.14 (SHIELD), R4972.2, R4982.2, R4983.2, U401.41 (GND), Y401.2 (G), Y401.4 (G); also elsewhere on the board
unnamed: C4951.1, R4951.2, R4952.2, R4953.2, R4954.2
unnamed: D401.1 (K), R4961.1
unnamed: D402.2 (A), R4971.2
unnamed: D403.2 (A), R4981.2
unnamed: R4951.1, T401.24 (MCT1)
unnamed: R4952.1, T401.21 (MCT2)
unnamed: R4953.1, T401.18 (MCT3)
unnamed: R4954.1, T401.15 (MCT4)
unnamed: C4911.1, T401.1 (TCT1)
unnamed: C4921.1, T401.4 (TCT2)
unnamed: C4931.1, T401.7 (TCT3)
unnamed: C4941.1, T401.10 (TCT4)
unnamed: C4901.1, R4915.2, R4916.2, U401.12 (PHYRSTB)
unnamed: R4912.2, U401.26 (RXCTL/PHYAD2)
unnamed: R4911.2, U401.27 (RXC/PHYAD1)
unnamed: R4910.2, U401.25 (RXD0/RXDLY)
unnamed: R4909.2, U401.24 (RXD1/TXDLY)
unnamed: R4908.2, U401.23 (RXD2/PLLOFF)
unnamed: R4907.2, U401.22 (RXD3/PHYAD0)
unnamed: R4905.2, U401.20 (TXC)
unnamed: R4906.2, U401.19 (TXCTL)
unnamed: R4904.2, U401.18 (TXD0)
unnamed: R4903.2, U401.17 (TXD1)
unnamed: R4902.2, U401.16 (TXD2)
unnamed: R4901.2, U401.15 (TXD3)
unnamed: R4961.2, R4962.2, U401.32 (LED0/CFG_EXT)
unnamed: R4971.1, R4972.1, U401.33 (LED1/CFG_LDO0)
unnamed: R4981.1, R4982.1, U401.34 (LED2/CFG_LDO1)
unnamed: C4976.2, U401.36 (XTAL_IN), Y401.1
unnamed: C4977.2, U401.37 (XTAL_OUT), Y401.3
unnamed: L401.1, U401.30 (REG_OUT)
unnamed: R4983.1, U401.39 (RSET)

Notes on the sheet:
RXD3 strap: PHYAD0 = 1, PHY address 1
RXD1 strap: TXDLY = 1 (4.7 k to DVDD_RG)
RGMII, 3.3 V, 125 MHz DDR
22 Ω each
Gigabit Ethernet: RTL8211F-CG, RGMII, discrete magnetics
four SEPARATE centre taps, 100 nF each
LED1: 100M link (active high); strap CFG_LDO0 = 0
switcher output 10 µF X5R, 100 nF per 1.0 V pin
RXD0 strap: RXDLY = 1 (4.7 k to DVDD_RG)
LED0: 10M link (active low); strap CFG_EXT = 1, 3.3 V I/O
LED2: 1000M link (active high); strap CFG_LDO1 = 0
MDIO, INTB, RST: 4.7 k up (MDIO's 1.5 k is for a long bus) RST: 330 Ω + 1 µF, ~10 ms after power
25 MHz, 12 pF crystal, 18 pF loads
22 Ω series resistors: source termination belongs at the driver, so TX (FPGA -> PHY) wants its resistors at the FPGA end and RX (PHY -> FPGA) at the PHY end. This board stands both columns beside the PHY (the TX ones move to the FPGA in rev B).
Bob Smith termination; the jack's shield goes to the same ground. The magnetics are the isolation (IEEE 802.3); this 1 nF / 3 kV 1812 is the designed bridge across it. The board has not been hipot-tested.
U401 RTL8211F-CG: one chip, drawn as RGMII side (A), line side (B) and power (C)
internal 1.0 V switcher output: feeds only this chip; the inductor must take 600 mA (a power inductor, not a chip one)
line driver current reference, 1 %
100 Ω differential pairs; P on the transformer's - ends, N on its + ends, both sides (see the layout)
AVDD33 x2, DVDD33, DVDD_RG: 100 nF each at the pin
+3V3_ETH is +3V3 through a ferrite bead (power sheet). Straps pulled up through 4.7 k: RXD3 (PHYAD = 1), RXD1 (TXDLY = 1), RXD0 (RXDLY = 1). The PHY's internal pull-ups would lose to the ECP5's pull-downs during configuration, when the straps are sampled: both 2 ns RGMII delays inside the PHY, so t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
The FPGA talks RGMII (4-bit DDR at 125 MHz) at 3.3 V to the PHY, through 22 Ω series resistors. The PHY makes its own 1.0 V core with an internal switcher (REG_OUT, 2.2 µH). Straps on the LED and RXD pins are sampled at reset: CFG_EXT = 1 (external 3.3 V on DVDD_RG), CFG_LDO[1:0] = 00 (3.3 V I/O pa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
